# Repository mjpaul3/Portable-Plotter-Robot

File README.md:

# Portable-Plotter-Robot
ECE445 Project Team 34

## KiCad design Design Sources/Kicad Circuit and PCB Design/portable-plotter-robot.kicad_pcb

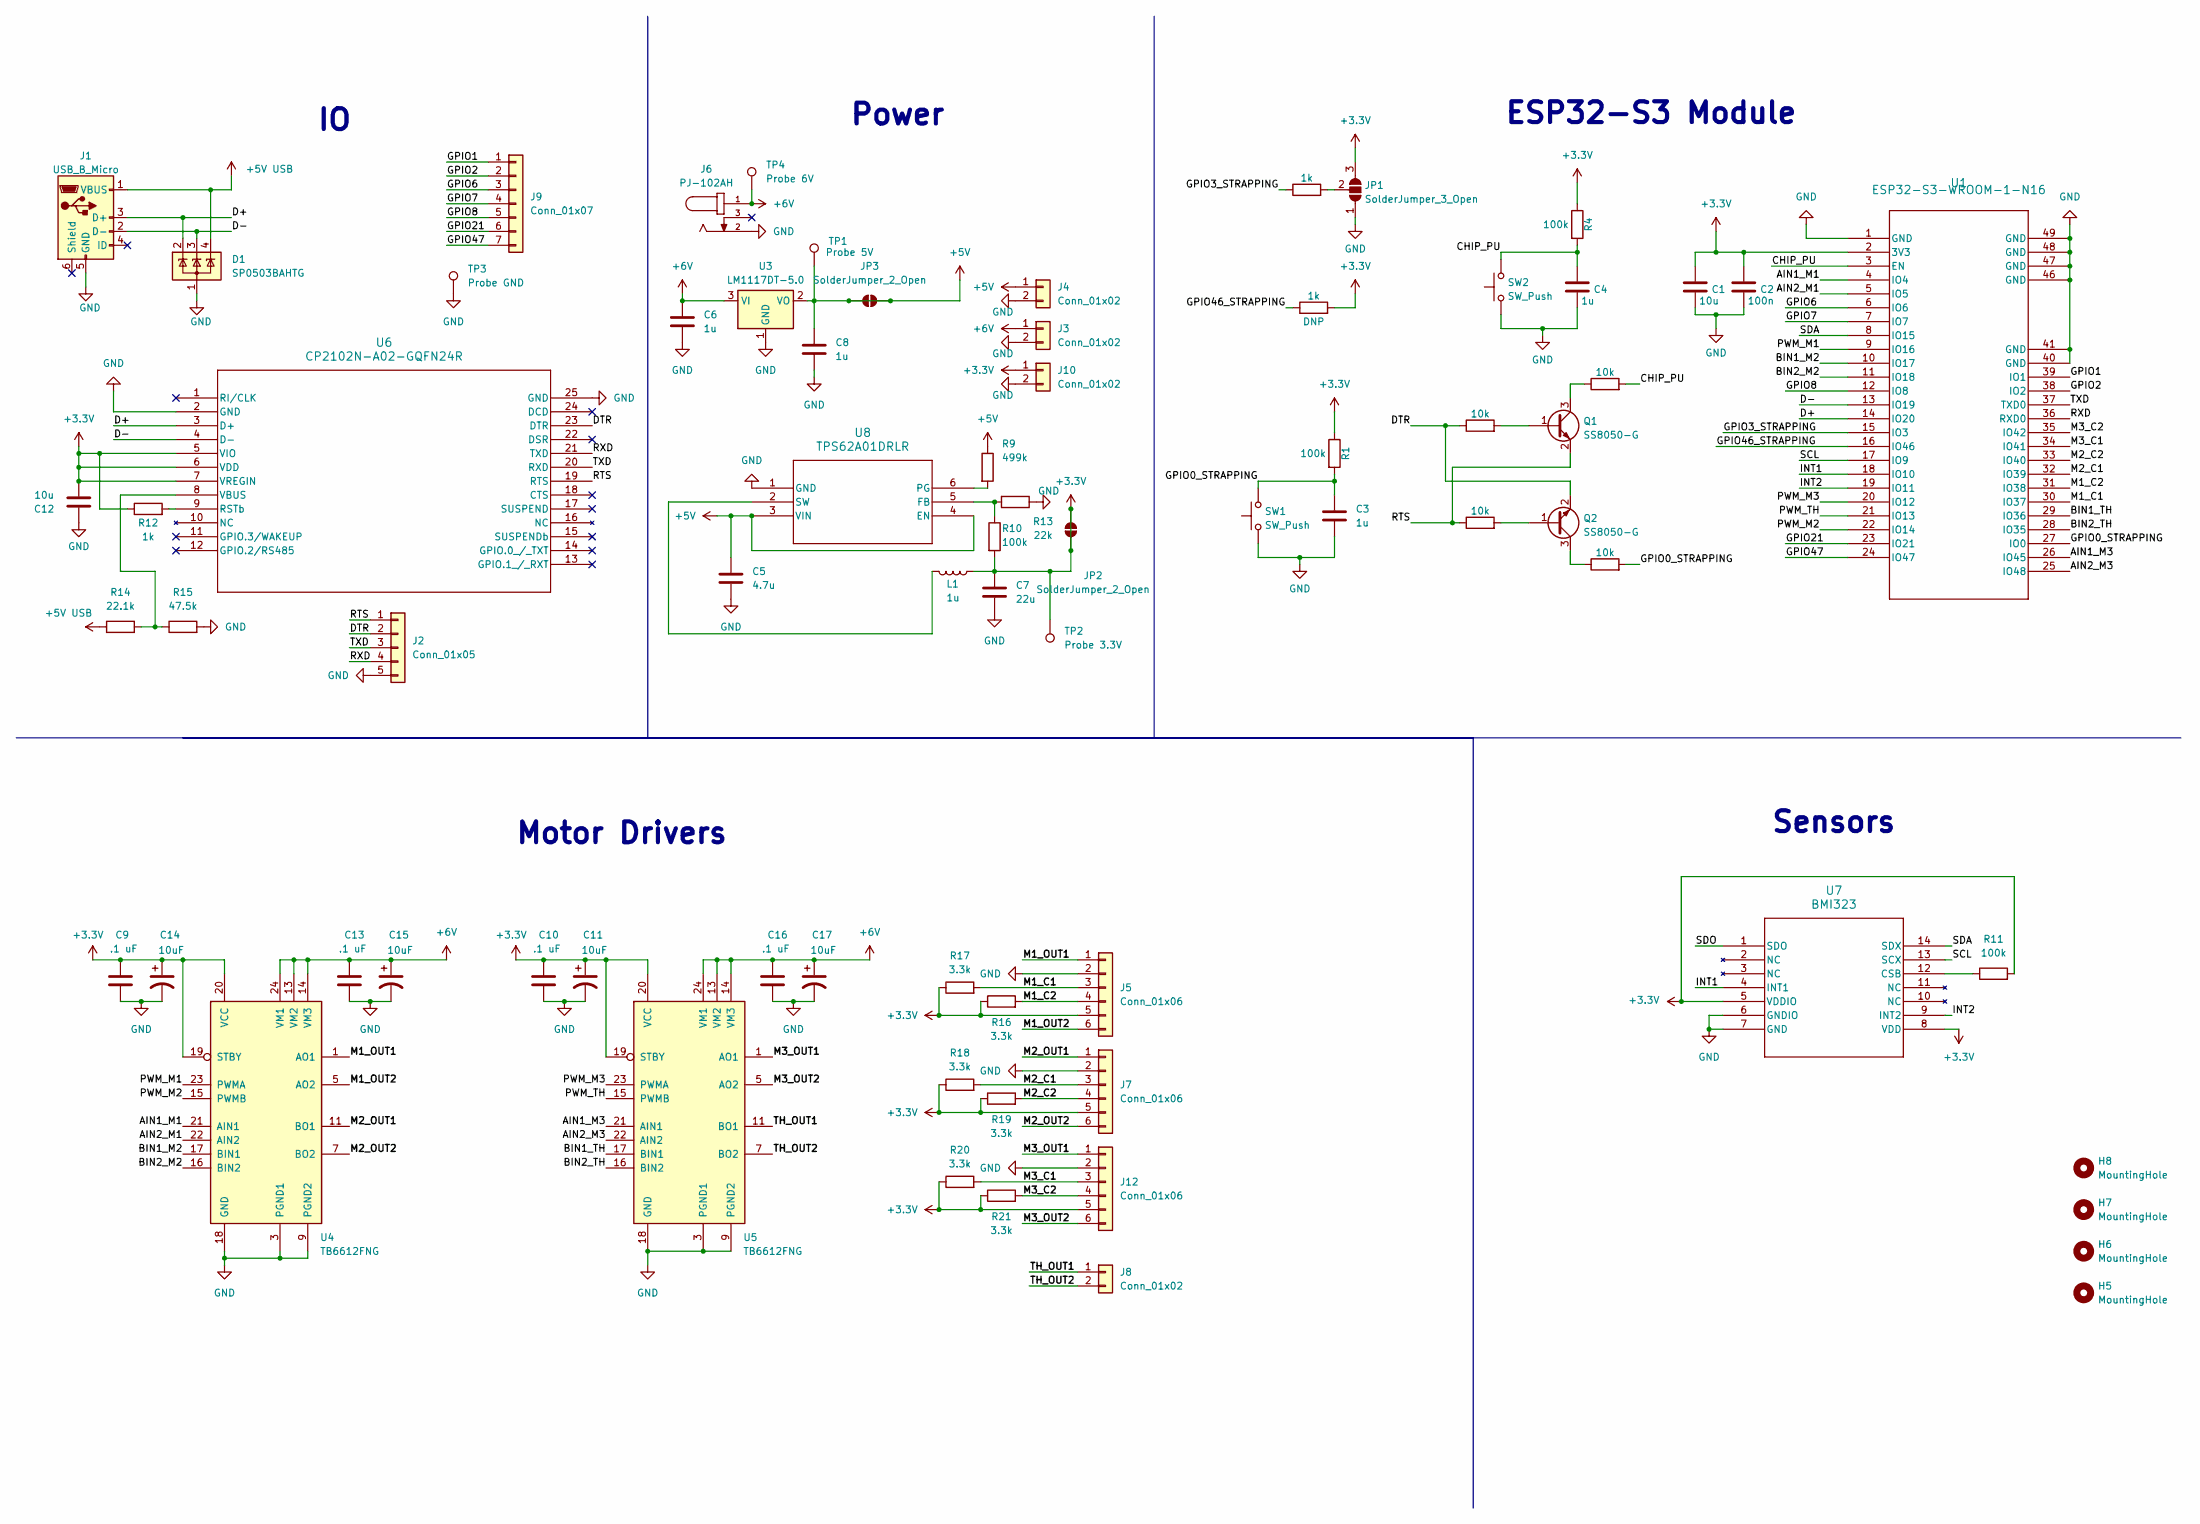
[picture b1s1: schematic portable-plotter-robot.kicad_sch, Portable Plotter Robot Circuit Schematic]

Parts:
C1, C12: 10u; C_0805_2012Metric_Pad1.18x1.45mm_HandSolder
C2: 100n; C_0805_2012Metric_Pad1.18x1.45mm_HandSolder
C3, C4, C6, C8: 1u; C_0805_2012Metric_Pad1.18x1.45mm_HandSolder
C5: 4.7u; C_0805_2012Metric_Pad1.18x1.45mm_HandSolder
C7: 22u; C_0805_2012Metric_Pad1.18x1.45mm_HandSolder
C9, C10, C13, C16: .1 uF; C_0805_2012Metric_Pad1.18x1.45mm_HandSolder
C11, C14, C15, C17: 10uF; CP_Radial_D5.0mm_P2.00mm
D1: SP0503BAHTG; SOT-143
H5, H6, H7, H8: MountingHole; MountingHole_3.2mm_M3
J1: USB_B_Micro; USB_Micro-B_Amphenol_10118194_Horizontal
J2: Conn_01x05; PinHeader_1x05_P2.54mm_Vertical
J3, J4, J8, J10: Conn_01x02; Molex_SL_171971-0002_1x02_P2.54mm_Vertical
J5, J7, J12: Conn_01x06; Molex_SL_171971-0006_1x06_P2.54mm_Vertical
J6: PJ-102AH; CUI_PJ-102AH; PART_REV 1.02
J9: Conn_01x07; PinHeader_1x07_P2.54mm_Vertical
JP1: SolderJumper_3_Open; SolderJumper-3_P1.3mm_Open_RoundedPad1.0x1.5mm
JP2, JP3: SolderJumper_2_Open; SolderJumper-2_P1.3mm_Open_RoundedPad1.0x1.5mm
L1: 1u; L_0805_2012Metric_Pad1.15x1.40mm_HandSolder
Q1, Q2: SS8050-G; SOT-23
R1, R4, R10, R11: 100k; R_0805_2012Metric_Pad1.20x1.40mm_HandSolder
R2, R3, R12: 1k; R_0805_2012Metric_Pad1.20x1.40mm_HandSolder
R5, R6, R7, R8: 10k; R_0805_2012Metric_Pad1.20x1.40mm_HandSolder
R9: 499k; R_0805_2012Metric_Pad1.20x1.40mm_HandSolder
R13: 22k; R_0805_2012Metric_Pad1.20x1.40mm_HandSolder
R14: 22.1k; R_0805_2012Metric_Pad1.20x1.40mm_HandSolder
R15: 47.5k; R_0805_2012Metric_Pad1.20x1.40mm_HandSolder
R16, R17, R18, R19, R20, R21: 3.3k; R_0805_2012Metric_Pad1.20x1.40mm_HandSolder
SW1, SW2: SW_Push; SW_Push_1P1T_NO_6x6mm_H9.5mm
TP1: Probe 5V; TestPoint_Plated_Hole_D2.0mm
TP2: Probe 3.3V; TestPoint_Plated_Hole_D2.0mm
TP3: Probe GND; TestPoint_Plated_Hole_D2.0mm
TP4: Probe 6V; TestPoint_Plated_Hole_D2.0mm
U1: ESP32-S3-WROOM-1-N16; ESP32-S3-WROOM-1_EXP
U3: LM1117DT-5.0; MP04A_TEX-M
U4, U5: TB6612FNG; SSOP-24_5.3x8.2mm_P0.65mm
U6: CP2102N-A02-GQFN24R; QFN24_SIL-M
U7: BMI323; XDCR_BMI270
U8: TPS62A01DRLR; SOT6_DRL_TEX-M

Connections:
+3.3V: C1.1, C2.1, C7.1, C9.1, C10.1, C11.1, C12.2, C14.1, J5.5, J7.5, J10.1, J12.5, JP1.3 (B), JP2.1 (A), JP2.2 (B), L1.1, R1.1, R3.2, R4.1, R10.2, R11.2, R12.1, R16.1, R17.1, R18.1, R19.1, R20.1, R21.1, TP2.1, U1.2 (3V3), U4.19 (STBY), U4.20 (VCC), U5.19 (STBY), U5.20 (VCC), U6.5 (VIO), U6.6 (VDD), U6.7 (VREGIN), U7.5 (VDDIO), U7.8 (VDD)
+5V: C5.1, C8.1, J4.1, JP3.1 (A), JP3.2 (B), R9.1, TP1.1, U3.2 (VO), U8.3 (VIN), U8.4 (EN)
+5V USB: D1.4 (K), J1.1 (VBUS), R14.1
+6V: C6.1, C13.1, C15.1, C16.1, C17.1, J3.1, J6.1, TP4.1, U3.3 (VI), U4.13 (VM2), U4.14 (VM3), U4.24 (VM1), U5.13 (VM2), U5.14 (VM3), U5.24 (VM1)
/AIN1_M1: U1.4 (IO4), U4.21 (AIN1)
/AIN1_M3: U1.26 (IO45), U5.21 (AIN1)
/AIN2_M1: U1.5 (IO5), U4.22 (AIN2)
/AIN2_M3: U1.25 (IO48), U5.22 (AIN2)
/BIN1_M2: U1.10 (IO17), U4.17 (BIN1)
/BIN1_TH: U1.29 (IO36), U5.17 (BIN1)
/BIN2_M2: U1.11 (IO18), U4.16 (BIN2)
/BIN2_TH: U1.28 (IO35), U5.16 (BIN2)
/CHIP_PU: C4.1, R4.2, R7.2, SW2.2, U1.3 (EN)
/D+: D1.2 (K), J1.3 (D+), U1.14 (IO20), U6.3 (D+)
/D-: D1.3 (K), J1.2 (D-), U1.13 (IO19), U6.4 (D-)
/DTR: J2.2, Q2.2 (E), R5.1, U6.23 (DTR)
/GPIO0_STRAPPING: C3.1, R1.2, R8.2, SW1.2, U1.27 (IO0)
/GPIO1: J9.1, U1.39 (IO1)
/GPIO2: J9.2, U1.38 (IO2)
/GPIO3_STRAPPING: R2.1, U1.15 (IO3)
/GPIO6: J9.3, U1.6 (IO6)
/GPIO7: J9.4, U1.7 (IO7)
/GPIO8: J9.5, U1.12 (IO8)
/GPIO21: J9.6, U1.23 (IO21)
/GPIO46_STRAPPING: R3.1, U1.16 (IO46)
/GPIO47: J9.7, U1.24 (IO47)
/INT1: U1.18 (IO10), U7.4 (INT1)
/INT2: U1.19 (IO11), U7.9 (INT2)
/M1_C1: J5.3, R17.2, U1.30 (IO37)
/M1_C2: J5.4, R16.2, U1.31 (IO38)
/M1_OUT1: J5.1, U4.1 (AO1), U4.2 (AO1)
/M1_OUT2: J5.6, U4.5 (AO2), U4.6 (AO2)
/M2_C1: J7.3, R18.2, U1.32 (IO39)
/M2_C2: J7.4, R19.2, U1.33 (IO40)
/M2_OUT1: J7.1, U4.11 (BO1), U4.12 (BO1)
/M2_OUT2: J7.6, U4.7 (BO2), U4.8 (BO2)
/M3_C1: J12.3, R20.2, U1.34 (IO41)
/M3_C2: J12.4, R21.2, U1.35 (IO42)
/M3_OUT1: J12.1, U5.1 (AO1), U5.2 (AO1)
/M3_OUT2: J12.6, U5.5 (AO2), U5.6 (AO2)
/PWM_M1: U1.9 (IO16), U4.23 (PWMA)
/PWM_M2: U1.22 (IO14), U4.15 (PWMB)
/PWM_M3: U1.20 (IO12), U5.23 (PWMA)
/PWM_TH: U1.21 (IO13), U5.15 (PWMB)
/RTS: J2.1, Q1.2 (E), R6.1, U6.19 (RTS)
/RXD: J2.4, U1.36 (RXD0), U6.21 (TXD)
/SCL: U1.17 (IO9), U7.13 (SCX)
/SDA: U1.8 (IO15), U7.14 (SDX)
/SDO: U7.1 (SDO)
/TH_OUT1: J8.1, U5.11 (BO1), U5.12 (BO1)
/TH_OUT2: J8.2, U5.7 (BO2), U5.8 (BO2)
/TXD: J2.3, U1.37 (TXD0), U6.20 (RXD)
GND: C1.2, C2.2, C3.2, C4.2, C5.2, C6.2, C7.2, C8.2, C9.2, C10.2, C11.2, C12.1, C13.2, C14.2, C15.2, C16.2, C17.2, D1.1 (A), J1.5 (GND), J2.5, J3.2, J4.2, J5.2, J6.2, J7.2, J10.2, J12.2, JP1.1 (A), R13.1, R15.2, SW1.1, SW2.1, TP3.1, U1.1 (GND), U1.40 (GND), U1.41 (GND), U1.46 (GND), U1.47 (GND), U1.48 (GND), U1.49 (GND), U3.1 (GND), U4.3 (PGND1), U4.4 (PGND1), U4.9 (PGND2), U4.10 (PGND2), U4.18 (GND), U5.3 (PGND1), U5.4 (PGND1), U5.9 (PGND2), U5.10 (PGND2), U5.18 (GND), U6.2 (GND), U6.25 (GND), U7.6 (GNDIO), U7.7 (GND), U8.1 (GND)
unnamed: JP1.2 (C), R2.2
unnamed: Q1.1 (B), R5.2
unnamed: Q1.3 (C), R7.1
unnamed: Q2.1 (B), R6.2
unnamed: Q2.3 (C), R8.1
unnamed: R12.2, U6.9 (RSTb)
unnamed: R14.2, R15.1, U6.8 (VBUS)
unnamed: R11.1, U7.12 (CSB)
unnamed: R10.1, R13.2, U8.5 (FB)
unnamed: R9.2, U8.6 (PG)
unnamed: L1.2, U8.2 (SW)

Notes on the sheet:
Power
Sensors
Motor Drivers
ESP32-S3 Module

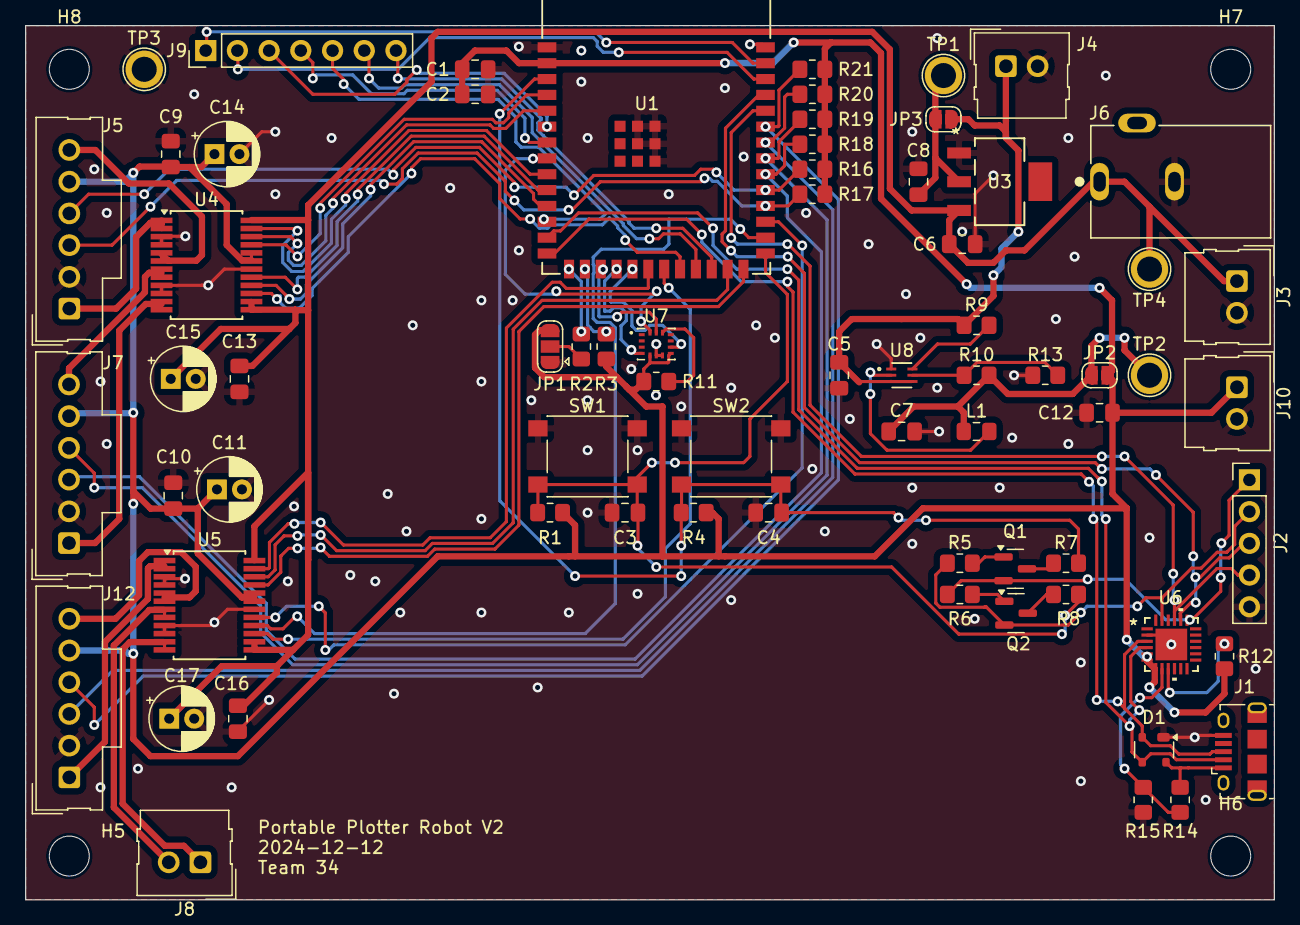
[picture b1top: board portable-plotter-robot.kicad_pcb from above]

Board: 2 copper layers, 100.0 x 70.0 mm, 73 parts (0 on the bottom side), 63 nets.

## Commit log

2024-12-12 ignore .DS_Store
2024-12-12 added folder structure and Kicad files
2024-12-12 added notebook folders
2024-12-12 Added files
2024-12-12 ESP32 repo added as submodule
2024-12-12 Added Sagnik3's notebook docs (mdbook)
2024-12-12 Added my NB entries
2024-12-12 Added summary updates
2024-12-12 Entries started
2024-12-12 Added initial entries- ported to MDbook
2024-12-12 Added Lab Notebook Files for Matthew Paul
2024-12-13 Test ya
2024-12-13 yessir
2024-12-13 newest
2024-12-13 Sagniks commits added
